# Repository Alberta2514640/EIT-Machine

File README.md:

# picoAWG
Arbitrary Waveform Generator for the Raspberry Pi Pico 16 Channels

## AWG Desktop Application
Desktop application to interface with Arbitrary Waveform Generator

TODO
- Implement Control of 16 Channels to Control Amplitude, Frequency, Offset 
- Read Back Output with Monitor to see the output
- Control LED s as needed

## PCB Design 
The board design for the waveform generator

TODO
- Update PCB design to include RP2040 directly and a cheaper OP AMP
- Update PCB design to shrink the design down to a more reasonable size and add a small status display beyond the current 5 status LEDs.

## RP2040 Code 
The code loaded onto the Pi Pico. 

TODO
- Monitor Output Needs to be fixed to setup the output
    - Write Values to the Output and Read Corresponding Voltage Changes 
- Control over channels 1-16 with Output Adjustments
    - Split the ADC control and the communication/ led control to seperate cores communicating between one another.
    - Utilize the PIO to drive the SPI peripheral and set the outputs appropriately. 
- Add functions to set the Configuration Register, Offset, Calibration, Data, Registers

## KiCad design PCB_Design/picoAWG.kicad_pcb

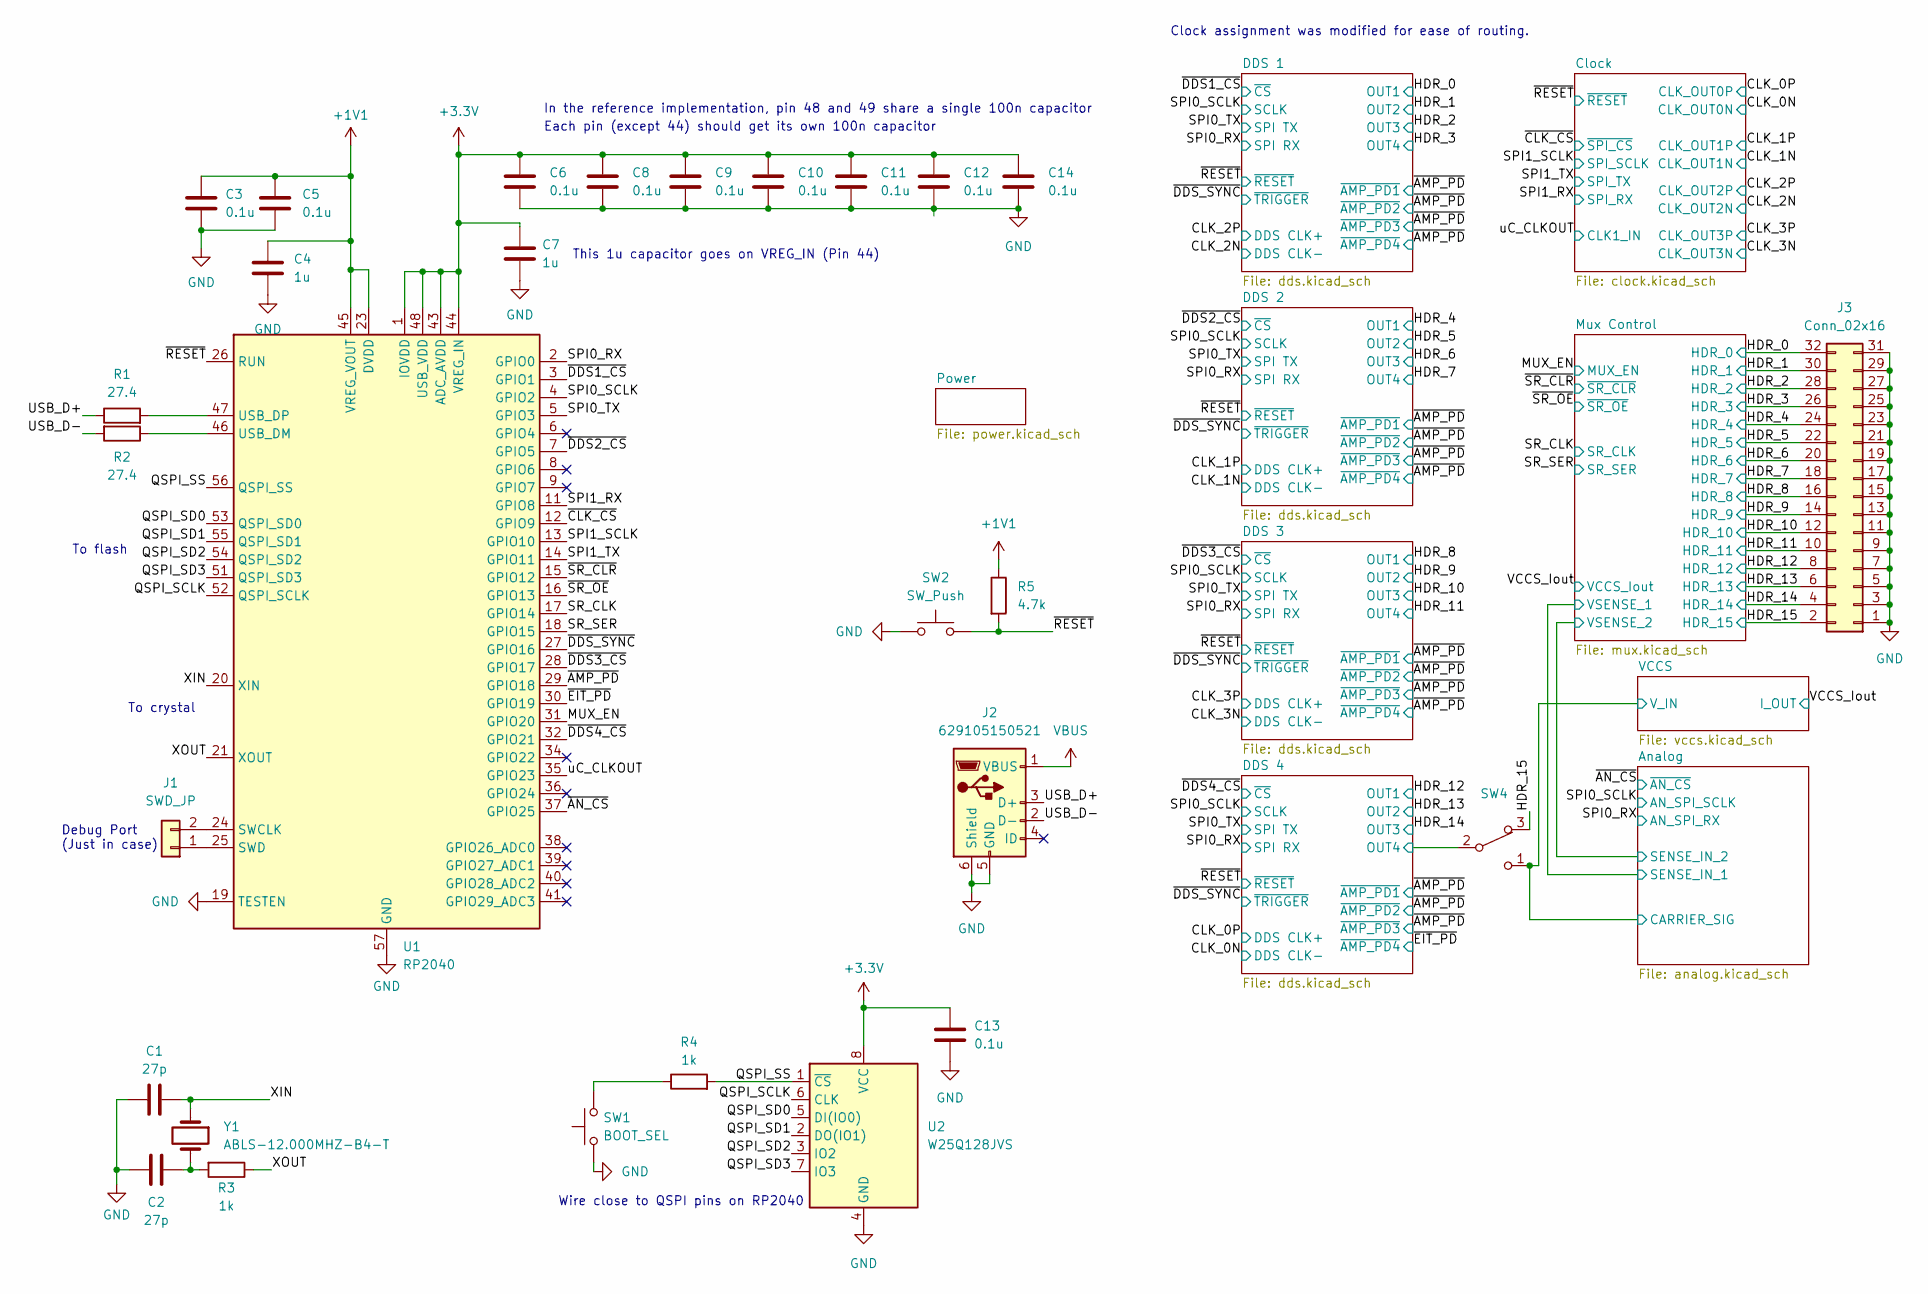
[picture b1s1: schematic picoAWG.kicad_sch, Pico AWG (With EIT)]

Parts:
C1, C2: 27p; C_0603_1608Metric
C3, C5, C6, C8, C9, C10, C11, C12, C13, C14: 0.1u; C_0603_1608Metric
C4, C7: 1u; C_0603_1608Metric
J1: SWD_JP; PinSocket_1x02_P1.00mm_Vertical
J2: 629105150521; USB_Micro-B_Amphenol_10118193-0001LF_Horizontal
J3: Conn_02x16; PinHeader_2x16_P2.54mm_Vertical
R1, R2: 27.4; R_0603_1608Metric
R3, R4: 1k; R_0603_1608Metric
R5: 4.7k; R_0603_1608Metric
SW1: BOOT_SEL; SW_Push_SPST_NO_Alps_SKRK
SW2: SW_Push; SW_Push_SPST_NO_Alps_SKRK
SW4: SW_SPDT_321; SW_E-Switch_EG1271_SPDT
U1: RP2040; QFN-56-1EP_7x7mm_P0.4mm_EP3.2x3.2mm
U2: W25Q128JVS; SOIC-8_5.23x5.23mm_P1.27mm
Y1: ABLS-12.000MHZ-B4-T; Crystal_SMD_HC49-SD

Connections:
+1V1: C3.1, C4.1, C5.1, R5.1, U1.23 (DVDD), U1.45 (VREG_VOUT), U1.50 (DVDD)
+3.3V: C6.1, C7.1, C8.1, C9.1, C10.1, C11.1, C12.1, C13.1, C14.1, U1.1 (IOVDD), U1.10 (IOVDD), U1.22 (IOVDD), U1.33 (IOVDD), U1.42 (IOVDD), U1.43 (ADC_AVDD), U1.44 (VREG_IN), U1.48 (USB_VDD), U1.49 (IOVDD), U2.8 (VCC); also elsewhere on the board
/Analog/CARRIER_SIG: SW4.1 (C); also elsewhere on the board
/DDS 4/OUT4: SW4.2 (B); also elsewhere on the board
/HDR_0: J3.32; also elsewhere on the board
/HDR_1: J3.30; also elsewhere on the board
/HDR_2: J3.28; also elsewhere on the board
/HDR_3: J3.26; also elsewhere on the board
/HDR_4: J3.24; also elsewhere on the board
/HDR_5: J3.22; also elsewhere on the board
/HDR_6: J3.20; also elsewhere on the board
/HDR_7: J3.18; also elsewhere on the board
/HDR_8: J3.16; also elsewhere on the board
/HDR_9: J3.14; also elsewhere on the board
/HDR_10: J3.12; also elsewhere on the board
/HDR_11: J3.10; also elsewhere on the board
/HDR_12: J3.8; also elsewhere on the board
/HDR_13: J3.6; also elsewhere on the board
/HDR_14: J3.4; also elsewhere on the board
/HDR_15: J3.2, SW4.3 (A); also elsewhere on the board
/MUX_EN: U1.31 (GPIO20); also elsewhere on the board
/QSPI_SCLK: U1.52 (QSPI_SCLK), U2.6 (CLK)
/QSPI_SD0: U1.53 (QSPI_SD0), U2.5 (DI(IO0))
/QSPI_SD1: U1.55 (QSPI_SD1), U2.2 (DO(IO1))
/QSPI_SD2: U1.54 (QSPI_SD2), U2.3 (IO2)
/QSPI_SD3: U1.51 (QSPI_SD3), U2.7 (IO3)
/QSPI_SS: R4.2, U1.56 (QSPI_SS), U2.1 (~CS)
/SPI0_RX: U1.2 (GPIO0); also elsewhere on the board
/SPI0_SCLK: U1.4 (GPIO2); also elsewhere on the board
/SPI0_TX: U1.5 (GPIO3); also elsewhere on the board
/SPI1_RX: U1.11 (GPIO8); also elsewhere on the board
/SPI1_SCLK: U1.13 (GPIO10); also elsewhere on the board
/SPI1_TX: U1.14 (GPIO11); also elsewhere on the board
/SR_CLK: U1.17 (GPIO14); also elsewhere on the board
/SR_SER: U1.18 (GPIO15); also elsewhere on the board
/USB_D+: J2.3 (D+), R1.1
/USB_D-: J2.2 (D-), R2.2
/XIN: C1.2, U1.20 (XIN), Y1.1
/XOUT: R3.1, U1.21 (XOUT)
/uC_CLKOUT: U1.35 (GPIO23); also elsewhere on the board
/~AMP_PD: U1.29 (GPIO18); also elsewhere on the board
/~AN_CS: U1.37 (GPIO25); also elsewhere on the board
/~CLK_CS: U1.12 (GPIO9); also elsewhere on the board
/~DDS1_CS: U1.3 (GPIO1); also elsewhere on the board
/~DDS2_CS: U1.7 (GPIO5); also elsewhere on the board
/~DDS3_CS: U1.28 (GPIO17); also elsewhere on the board
/~DDS4_CS: U1.32 (GPIO21); also elsewhere on the board
/~DDS_SYNC: U1.27 (GPIO16); also elsewhere on the board
/~EIT_PD: U1.30 (GPIO19); also elsewhere on the board
/~RESET: R5.2, SW2.2, U1.26 (RUN); also elsewhere on the board
/~SR_CLR: U1.15 (GPIO12); also elsewhere on the board
/~SR_OE: U1.16 (GPIO13); also elsewhere on the board
GND: C1.1, C2.2, C3.2, C4.2, C5.2, C6.2, C7.2, C8.2, C9.2, C10.2, C11.2, C12.2, C13.2, C14.2, J2.5 (GND), J2.6 (Shield), J3.1, J3.3, J3.5, J3.7, J3.9, J3.11, J3.13, J3.15, J3.17, J3.19, J3.21, J3.23, J3.25, J3.27, J3.29, J3.31, SW1.1, SW2.1, U1.19 (TESTEN), U1.57 (GND), U2.4 (GND); also elsewhere on the board
unnamed: C2.1, R3.2, Y1.2
unnamed: J1.1, U1.25 (SWD)
unnamed: J1.2, U1.24 (SWCLK)
unnamed: R4.1, SW1.2
unnamed: R2.1, U1.46 (USB_DM)
unnamed: R1.2, U1.47 (USB_DP)
VBUS: J2.1 (VBUS); also elsewhere on the board

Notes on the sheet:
Each pin (except 44) should get its own 100n capacitor
To crystal
Debug Port (Just in case)
This 1u capacitor goes on VREG_IN (Pin 44)
To flash
Clock assignment was modified for ease of routing.
In the reference implementation, pin 48 and 49 share a single 100n capacitor
Wire close to QSPI pins on RP2040

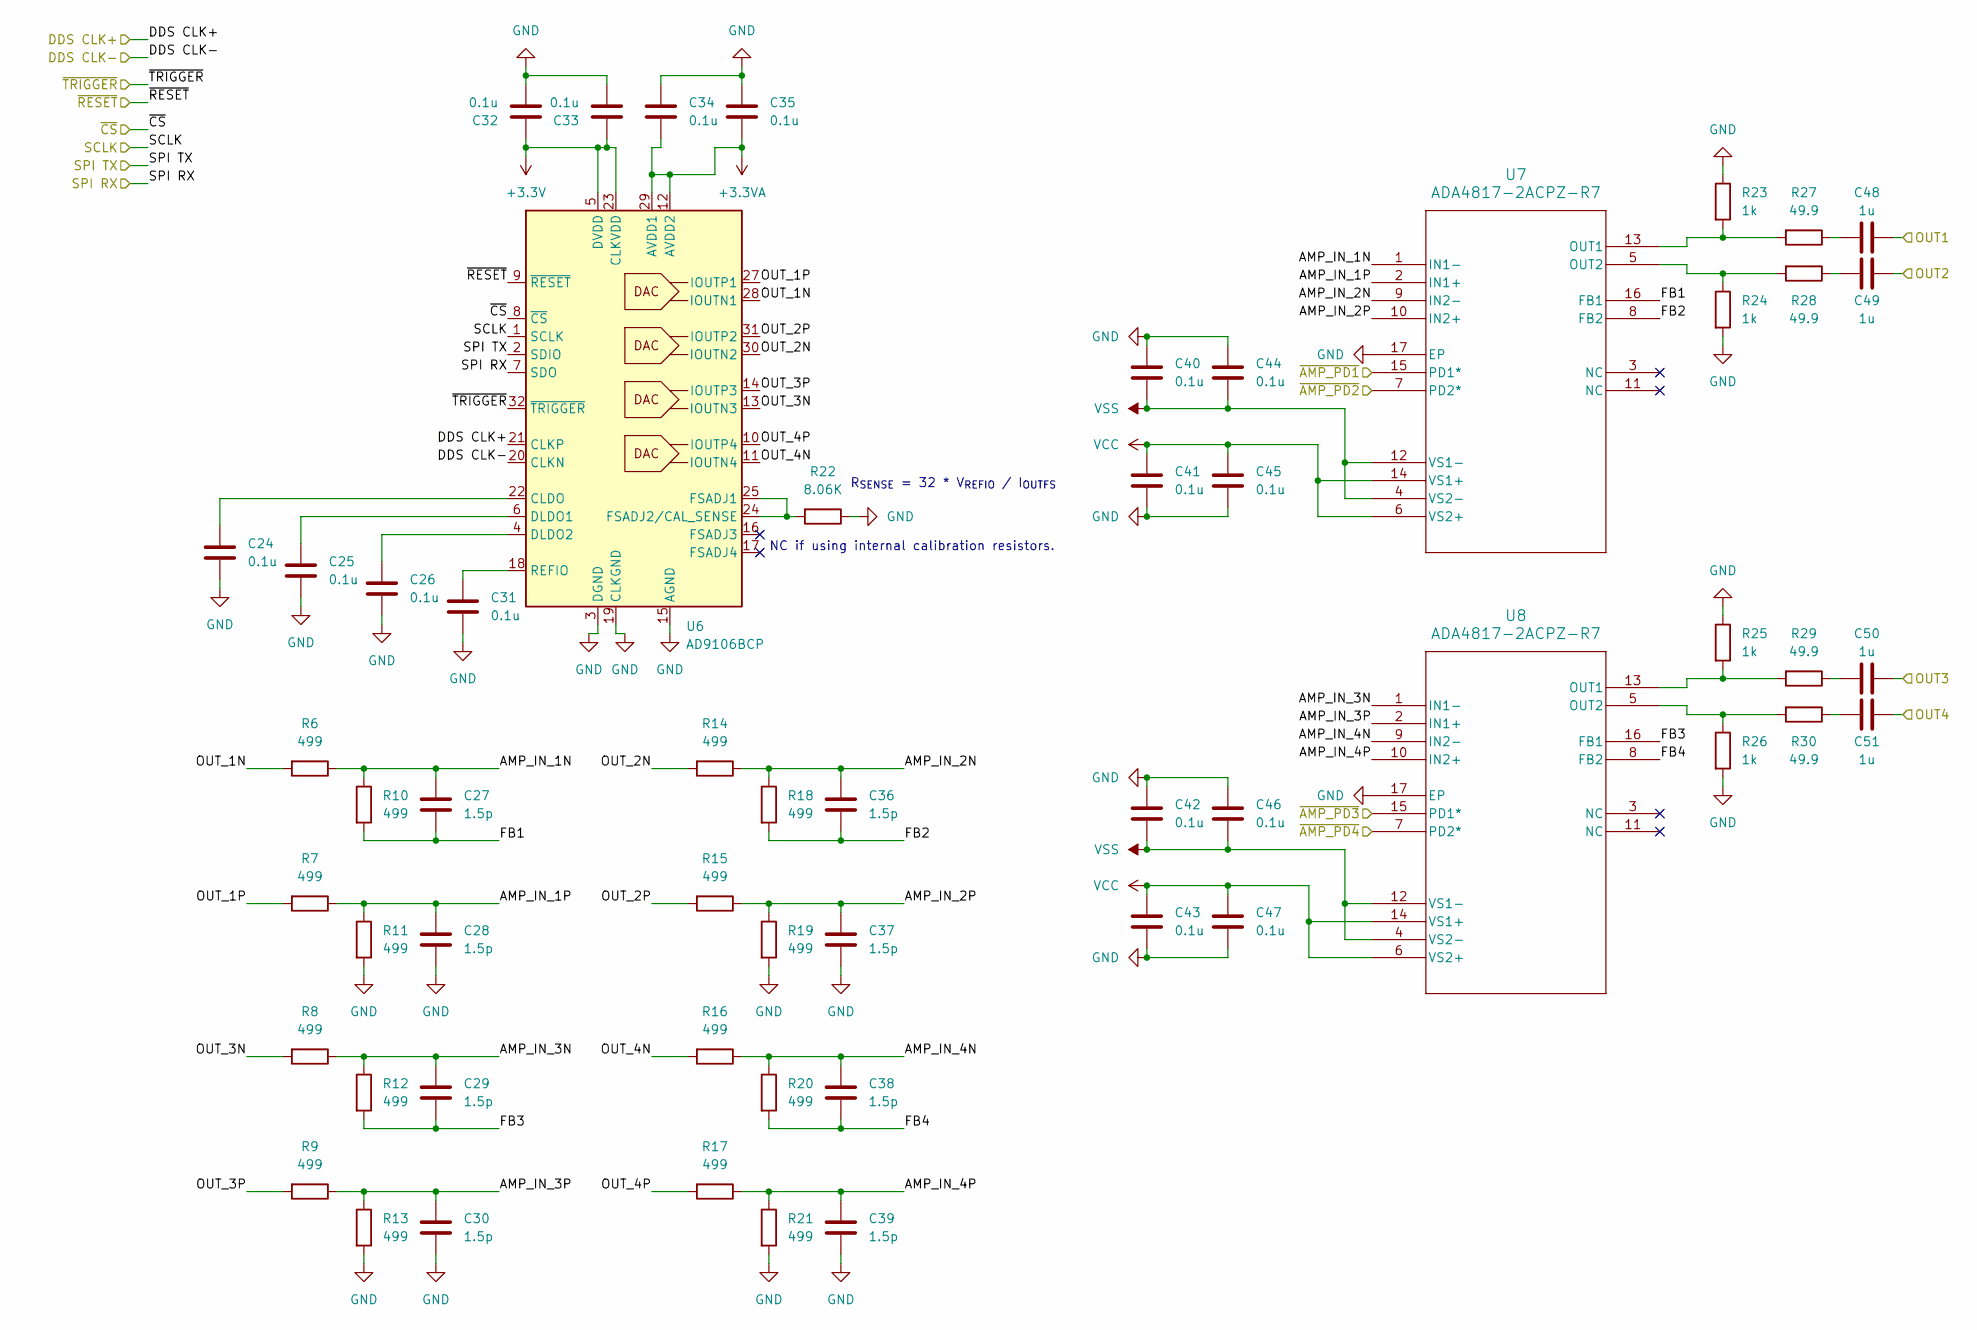
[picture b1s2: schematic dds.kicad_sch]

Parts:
C24, C25, C26, C31, C32, C33, C34, C35, C40, C41, C42, C43, C44, C45, C46, C47: 0.1u; C_0603_1608Metric
C27, C28, C29, C30, C36, C37, C38, C39: 1.5p; C_0603_1608Metric
C48, C49, C50, C51: 1u; C_0603_1608Metric
R6, R7, R8, R9, R10, R11, R12, R13, R14, R15, R16, R17, R18, R19, R20, R21: 499; R_0603_1608Metric
R22: 8.06K; R_0603_1608Metric
R23, R24, R25, R26: 1k; R_0603_1608Metric
R27, R28, R29, R30: 49.9; R_0603_1608Metric
U6: AD9106BCP; LFCSP-32-1EP_5x5mm_P0.5mm_EP3.6x3.6mm
U7, U8: ADA4817-2ACPZ-R7; CP_16_4_ADI

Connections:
+3.3V: C32.1, C33.1, U6.5 (DVDD), U6.23 (CLKVDD); also elsewhere on the board
+3.3VA: C34.2, C35.2, U6.12 (AVDD2), U6.29 (AVDD1); also elsewhere on the board
/CLK_2N: U6.20 (CLKN); also elsewhere on the board
/CLK_2P: U6.21 (CLKP); also elsewhere on the board
/DDS 1/AMP_IN_1N: C27.1, R6.1, R10.1, U7.1 (IN1-)
/DDS 1/AMP_IN_1P: C28.1, R7.1, R11.1, U7.2 (IN1+)
/DDS 1/AMP_IN_2N: C36.1, R14.1, R18.1, U7.9 (IN2-)
/DDS 1/AMP_IN_2P: C37.1, R15.1, R19.1, U7.10 (IN2+)
/DDS 1/AMP_IN_3N: C29.1, R8.1, R12.1, U8.1 (IN1-)
/DDS 1/AMP_IN_3P: C30.1, R9.1, R13.1, U8.2 (IN1+)
/DDS 1/AMP_IN_4N: C38.1, R16.1, R20.1, U8.9 (IN2-)
/DDS 1/AMP_IN_4P: C39.1, R17.1, R21.1, U8.10 (IN2+)
/DDS 1/FB1: C27.2, R10.2, U7.16 (FB1)
/DDS 1/FB2: C36.2, R18.2, U7.8 (FB2)
/DDS 1/FB3: C29.2, R12.2, U8.16 (FB1)
/DDS 1/FB4: C38.2, R20.2, U8.8 (FB2)
/DDS 1/OUT_1N: R6.2, U6.28 (IOUTN1)
/DDS 1/OUT_1P: R7.2, U6.27 (IOUTP1)
/DDS 1/OUT_2N: R14.2, U6.30 (IOUTN2)
/DDS 1/OUT_2P: R15.2, U6.31 (IOUTP2)
/DDS 1/OUT_3N: R8.2, U6.13 (IOUTN3)
/DDS 1/OUT_3P: R9.2, U6.14 (IOUTP3)
/DDS 1/OUT_4N: R16.2, U6.11 (IOUTN4)
/DDS 1/OUT_4P: R17.2, U6.10 (IOUTP4)
/HDR_0: C48.2; also elsewhere on the board
/HDR_1: C49.2; also elsewhere on the board
/HDR_2: C50.2; also elsewhere on the board
/HDR_3: C51.2; also elsewhere on the board
/SPI0_RX: U6.7 (SDO); also elsewhere on the board
/SPI0_SCLK: U6.1 (SCLK); also elsewhere on the board
/SPI0_TX: U6.2 (SDIO); also elsewhere on the board
/~AMP_PD: U7.7 (PD2*), U7.15 (PD1*), U8.7 (PD2*), U8.15 (PD1*); also elsewhere on the board
/~DDS1_CS: U6.8 (~CS); also elsewhere on the board
/~DDS_SYNC: U6.32 (~TRIGGER); also elsewhere on the board
/~RESET: U6.9 (~RESET); also elsewhere on the board
GND: C24.1, C25.1, C26.1, C28.2, C30.2, C31.1, C32.2, C33.2, C34.1, C35.1, C37.2, C39.2, C40.1, C41.2, C42.1, C43.2, C44.1, C45.2, C46.1, C47.2, R11.2, R13.2, R19.2, R21.2, R22.1, R23.1, R24.2, R25.1, R26.2, U6.3 (DGND), U6.15 (AGND), U6.19 (CLKGND), U6.26 (AGND), U6.33 (DGND), U7.17 (EP), U8.17 (EP); also elsewhere on the board
unnamed: C48.1, R27.1
unnamed: C49.1, R28.1
unnamed: C50.1, R29.1
unnamed: C51.1, R30.1
unnamed: C24.2, U6.22 (CLDO)
unnamed: C25.2, U6.6 (DLDO1)
unnamed: C26.2, U6.4 (DLDO2)
unnamed: R22.2, U6.24 (FSADJ2/CAL_SENSE), U6.25 (FSADJ1)
unnamed: C31.2, U6.18 (REFIO)
unnamed: R23.2, R27.2, U7.13 (OUT1)
unnamed: R24.1, R28.2, U7.5 (OUT2)
unnamed: R25.2, R29.2, U8.13 (OUT1)
unnamed: R26.1, R30.2, U8.5 (OUT2)
VCC: C41.1, C43.1, C45.1, C47.1, U7.6 (VS2+), U7.14 (VS1+), U8.6 (VS2+), U8.14 (VS1+); also elsewhere on the board
VSS: C40.2, C42.2, C44.2, C46.2, U7.4 (VS2-), U7.12 (VS1-), U8.4 (VS2-), U8.12 (VS1-); also elsewhere on the board

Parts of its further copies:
C52, C53, C54, C59, C60, C61, C62, C63, C68, C69, C70, C71, C72, C73, C74, C75, C80, C81, C82, C87, C88, C89, C90, C91, C96, C97, C98, C99, C100, C101, C102, C103, C108, C109, C110, C115, C116, C117, C118, C119, C124, C125, C126, C127, C128, C129, C130, C131: 0.1u; C_0603_1608Metric
C55, C56, C57, C58, C64, C65, C66, C67, C83, C84, C85, C86, C92, C93, C94, C95, C111, C112, C113, C114, C120, C121, C122, C123: 1.5p; C_0603_1608Metric
C76, C77, C78, C79, C104, C105, C106, C107, C132, C133, C134, C135: 1u; C_0603_1608Metric
R31, R32, R33, R34, R35, R36, R37, R38, R39, R40, R41, R42, R43, R44, R45, R46, R56, R57, R58, R59, R60, R61, R62, R63, R64, R65, R66, R67, R68, R69, R70, R71, R81, R82, R83, R84, R85, R86, R87, R88, R89, R90, R91, R92, R93, R94, R95, R96: 499; R_0603_1608Metric
R47, R72, R97: 8.06K; R_0603_1608Metric
R48, R49, R50, R51, R73, R74, R75, R76, R98, R99, R100, R101: 1k; R_0603_1608Metric
R52, R53, R54, R55, R77, R78, R79, R80, R102, R103, R104, R105: 49.9; R_0603_1608Metric
U9, U12, U15: AD9106BCP; LFCSP-32-1EP_5x5mm_P0.5mm_EP3.6x3.6mm
U10, U11, U13, U14, U16, U17: ADA4817-2ACPZ-R7; CP_16_4_ADI

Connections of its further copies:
+3.3V: C60.1, C61.1, C88.1, C89.1, C116.1, C117.1, U9.5 (DVDD), U9.23 (CLKVDD), U12.5 (DVDD), U12.23 (CLKVDD), U15.5 (DVDD), U15.23 (CLKVDD); also elsewhere on the board
+3.3VA: C62.2, C63.2, C90.2, C91.2, C118.2, C119.2, U9.12 (AVDD2), U9.29 (AVDD1), U12.12 (AVDD2), U12.29 (AVDD1), U15.12 (AVDD2), U15.29 (AVDD1); also elsewhere on the board
/CLK_0N: U15.20 (CLKN); also elsewhere on the board
/CLK_0P: U15.21 (CLKP); also elsewhere on the board
/CLK_1N: U9.20 (CLKN); also elsewhere on the board
/CLK_1P: U9.21 (CLKP); also elsewhere on the board
/CLK_3N: U12.20 (CLKN); also elsewhere on the board
/CLK_3P: U12.21 (CLKP); also elsewhere on the board
/DDS 2/AMP_IN_1N: C55.1, R31.1, R35.1, U10.1 (IN1-)
/DDS 2/AMP_IN_1P: C56.1, R32.1, R36.1, U10.2 (IN1+)
/DDS 2/AMP_IN_2N: C64.1, R39.1, R43.1, U10.9 (IN2-)
/DDS 2/AMP_IN_2P: C65.1, R40.1, R44.1, U10.10 (IN2+)
/DDS 2/AMP_IN_3N: C57.1, R33.1, R37.1, U11.1 (IN1-)
/DDS 2/AMP_IN_3P: C58.1, R34.1, R38.1, U11.2 (IN1+)
/DDS 2/AMP_IN_4N: C66.1, R41.1, R45.1, U11.9 (IN2-)
/DDS 2/AMP_IN_4P: C67.1, R42.1, R46.1, U11.10 (IN2+)
/DDS 2/FB1: C55.2, R35.2, U10.16 (FB1)
/DDS 2/FB2: C64.2, R43.2, U10.8 (FB2)
/DDS 2/FB3: C57.2, R37.2, U11.16 (FB1)
/DDS 2/FB4: C66.2, R45.2, U11.8 (FB2)
/DDS 2/OUT_1N: R31.2, U9.28 (IOUTN1)
/DDS 2/OUT_1P: R32.2, U9.27 (IOUTP1)
/DDS 2/OUT_2N: R39.2, U9.30 (IOUTN2)
/DDS 2/OUT_2P: R40.2, U9.31 (IOUTP2)
/DDS 2/OUT_3N: R33.2, U9.13 (IOUTN3)
/DDS 2/OUT_3P: R34.2, U9.14 (IOUTP3)
/DDS 2/OUT_4N: R41.2, U9.11 (IOUTN4)
/DDS 2/OUT_4P: R42.2, U9.10 (IOUTP4)
/DDS 3/AMP_IN_1N: C83.1, R56.1, R60.1, U13.1 (IN1-)
/DDS 3/AMP_IN_1P: C84.1, R57.1, R61.1, U13.2 (IN1+)
/DDS 3/AMP_IN_2N: C92.1, R64.1, R68.1, U13.9 (IN2-)
/DDS 3/AMP_IN_2P: C93.1, R65.1, R69.1, U13.10 (IN2+)
/DDS 3/AMP_IN_3N: C85.1, R58.1, R62.1, U14.1 (IN1-)
/DDS 3/AMP_IN_3P: C86.1, R59.1, R63.1, U14.2 (IN1+)
/DDS 3/AMP_IN_4N: C94.1, R66.1, R70.1, U14.9 (IN2-)
/DDS 3/AMP_IN_4P: C95.1, R67.1, R71.1, U14.10 (IN2+)
/DDS 3/FB1: C83.2, R60.2, U13.16 (FB1)
/DDS 3/FB2: C92.2, R68.2, U13.8 (FB2)
/DDS 3/FB3: C85.2, R62.2, U14.16 (FB1)
/DDS 3/FB4: C94.2, R70.2, U14.8 (FB2)
/DDS 3/OUT_1N: R56.2, U12.28 (IOUTN1)
/DDS 3/OUT_1P: R57.2, U12.27 (IOUTP1)
/DDS 3/OUT_2N: R64.2, U12.30 (IOUTN2)
/DDS 3/OUT_2P: R65.2, U12.31 (IOUTP2)
/DDS 3/OUT_3N: R58.2, U12.13 (IOUTN3)
/DDS 3/OUT_3P: R59.2, U12.14 (IOUTP3)
/DDS 3/OUT_4N: R66.2, U12.11 (IOUTN4)
/DDS 3/OUT_4P: R67.2, U12.10 (IOUTP4)
/DDS 4/AMP_IN_1N: C111.1, R81.1, R85.1, U16.1 (IN1-)
/DDS 4/AMP_IN_1P: C112.1, R82.1, R86.1, U16.2 (IN1+)
/DDS 4/AMP_IN_2N: C120.1, R89.1, R93.1, U16.9 (IN2-)
/DDS 4/AMP_IN_2P: C121.1, R90.1, R94.1, U16.10 (IN2+)
/DDS 4/AMP_IN_3N: C113.1, R83.1, R87.1, U17.1 (IN1-)
/DDS 4/AMP_IN_3P: C114.1, R84.1, R88.1, U17.2 (IN1+)
/DDS 4/AMP_IN_4N: C122.1, R91.1, R95.1, U17.9 (IN2-)
/DDS 4/AMP_IN_4P: C123.1, R92.1, R96.1, U17.10 (IN2+)
/DDS 4/FB1: C111.2, R85.2, U16.16 (FB1)
/DDS 4/FB2: C120.2, R93.2, U16.8 (FB2)
/DDS 4/FB3: C113.2, R87.2, U17.16 (FB1)
/DDS 4/FB4: C122.2, R95.2, U17.8 (FB2)
/DDS 4/OUT4: C135.2; also elsewhere on the board
/DDS 4/OUT_1N: R81.2, U15.28 (IOUTN1)
/DDS 4/OUT_1P: R82.2, U15.27 (IOUTP1)
/DDS 4/OUT_2N: R89.2, U15.30 (IOUTN2)
/DDS 4/OUT_2P: R90.2, U15.31 (IOUTP2)
/DDS 4/OUT_3N: R83.2, U15.13 (IOUTN3)
/DDS 4/OUT_3P: R84.2, U15.14 (IOUTP3)
/DDS 4/OUT_4N: R91.2, U15.11 (IOUTN4)
/DDS 4/OUT_4P: R92.2, U15.10 (IOUTP4)
/HDR_4: C76.2; also elsewhere on the board
/HDR_5: C77.2; also elsewhere on the board
/HDR_6: C78.2; also elsewhere on the board
/HDR_7: C79.2; also elsewhere on the board
/HDR_8: C104.2; also elsewhere on the board
/HDR_9: C105.2; also elsewhere on the board
/HDR_10: C106.2; also elsewhere on the board
/HDR_11: C107.2; also elsewhere on the board
/HDR_12: C132.2; also elsewhere on the board
/HDR_13: C133.2; also elsewhere on the board
/HDR_14: C134.2; also elsewhere on the board
/SPI0_RX: U9.7 (SDO), U12.7 (SDO), U15.7 (SDO); also elsewhere on the board
/SPI0_SCLK: U9.1 (SCLK), U12.1 (SCLK), U15.1 (SCLK); also elsewhere on the board
/SPI0_TX: U9.2 (SDIO), U12.2 (SDIO), U15.2 (SDIO); also elsewhere on the board
/~AMP_PD: U10.7 (PD2*), U10.15 (PD1*), U11.7 (PD2*), U11.15 (PD1*), U13.7 (PD2*), U13.15 (PD1*), U14.7 (PD2*), U14.15 (PD1*), U16.7 (PD2*), U16.15 (PD1*), U17.15 (PD1*); also elsewhere on the board
/~DDS2_CS: U9.8 (~CS); also elsewhere on the board
/~DDS3_CS: U12.8 (~CS); also elsewhere on the board
/~DDS4_CS: U15.8 (~CS); also elsewhere on the board
/~DDS_SYNC: U9.32 (~TRIGGER), U12.32 (~TRIGGER), U15.32 (~TRIGGER); also elsewhere on the board
/~EIT_PD: U17.7 (PD2*); also elsewhere on the board
/~RESET: U9.9 (~RESET), U12.9 (~RESET), U15.9 (~RESET); also elsewhere on the board
GND: C52.1, C53.1, C54.1, C56.2, C58.2, C59.1, C60.2, C61.2, C62.1, C63.1, C65.2, C67.2, C68.1, C69.2, C70.1, C71.2, C72.1, C73.2, C74.1, C75.2, C80.1, C81.1, C82.1, C84.2, C86.2, C87.1, C88.2, C89.2, C90.1, C91.1, C93.2, C95.2, C96.1, C97.2, C98.1, C99.2, C100.1, C101.2, C102.1, C103.2, C108.1, C109.1, C110.1, C112.2, C114.2, C115.1, C116.2, C117.2, C118.1, C119.1, C121.2, C123.2, C124.1, C125.2, C126.1, C127.2, C128.1, C129.2, C130.1, C131.2, R36.2, R38.2, R44.2, R46.2, R47.1, R48.1, R49.2, R50.1, R51.2, R61.2, R63.2, R69.2, R71.2, R72.1, R73.1, R74.2, R75.1, R76.2, R86.2, R88.2, R94.2, R96.2, R97.1, R98.1, R99.2, R100.1, R101.2, U9.3 (DGND), U9.15 (AGND), U9.19 (CLKGND), U9.26 (AGND), U9.33 (DGND), U10.17 (EP), U11.17 (EP), U12.3 (DGND), U12.15 (AGND), U12.19 (CLKGND), U12.26 (AGND), U12.33 (DGND), U13.17 (EP), U14.17 (EP), U15.3 (DGND), U15.15 (AGND), U15.19 (CLKGND), U15.26 (AGND), U15.33 (DGND), U16.17 (EP), U17.17 (EP); also elsewhere on the board
unnamed: C76.1, R52.1
unnamed: C77.1, R53.1
unnamed: C78.1, R54.1
unnamed: C79.1, R55.1
unnamed: C104.1, R77.1
unnamed: C105.1, R78.1
unnamed: C106.1, R79.1
unnamed: C107.1, R80.1
unnamed: C132.1, R102.1
unnamed: C133.1, R103.1
unnamed: C134.1, R104.1
unnamed: C135.1, R105.1
unnamed: C52.2, U9.22 (CLDO)
unnamed: C53.2, U9.6 (DLDO1)
unnamed: C54.2, U9.4 (DLDO2)
unnamed: R47.2, U9.24 (FSADJ2/CAL_SENSE), U9.25 (FSADJ1)
unnamed: C59.2, U9.18 (REFIO)
unnamed: R48.2, R52.2, U10.13 (OUT1)
unnamed: R49.1, R53.2, U10.5 (OUT2)
unnamed: R50.2, R54.2, U11.13 (OUT1)
unnamed: R51.1, R55.2, U11.5 (OUT2)
unnamed: C80.2, U12.22 (CLDO)
unnamed: C81.2, U12.6 (DLDO1)
unnamed: C82.2, U12.4 (DLDO2)
unnamed: R72.2, U12.24 (FSADJ2/CAL_SENSE), U12.25 (FSADJ1)
unnamed: C87.2, U12.18 (REFIO)
unnamed: R73.2, R77.2, U13.13 (OUT1)
unnamed: R74.1, R78.2, U13.5 (OUT2)
unnamed: R75.2, R79.2, U14.13 (OUT1)
unnamed: R76.1, R80.2, U14.5 (OUT2)
unnamed: C108.2, U15.22 (CLDO)
unnamed: C109.2, U15.6 (DLDO1)
unnamed: C110.2, U15.4 (DLDO2)
unnamed: R97.2, U15.24 (FSADJ2/CAL_SENSE), U15.25 (FSADJ1)
unnamed: C115.2, U15.18 (REFIO)
unnamed: R98.2, R102.2, U16.13 (OUT1)
unnamed: R99.1, R103.2, U16.5 (OUT2)
unnamed: R100.2, R104.2, U17.13 (OUT1)
unnamed: R101.1, R105.2, U17.5 (OUT2)
VCC: C69.1, C71.1, C73.1, C75.1, C97.1, C99.1, C101.1, C103.1, C125.1, C127.1, C129.1, C131.1, U10.6 (VS2+), U10.14 (VS1+), U11.6 (VS2+), U11.14 (VS1+), U13.6 (VS2+), U13.14 (VS1+), U14.6 (VS2+), U14.14 (VS1+), U16.6 (VS2+), U16.14 (VS1+), U17.6 (VS2+), U17.14 (VS1+); also elsewhere on the board
VSS: C68.2, C70.2, C72.2, C74.2, C96.2, C98.2, C100.2, C102.2, C124.2, C126.2, C128.2, C130.2, U10.4 (VS2-), U10.12 (VS1-), U11.4 (VS2-), U11.12 (VS1-), U13.4 (VS2-), U13.12 (VS1-), U14.4 (VS2-), U14.12 (VS1-), U16.4 (VS2-), U16.12 (VS1-), U17.4 (VS2-), U17.12 (VS1-); also elsewhere on the board

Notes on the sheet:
R_{SENSE} = 32 * V_{REFIO} / I_{OUTFS}
NC if using internal calibration resistors.

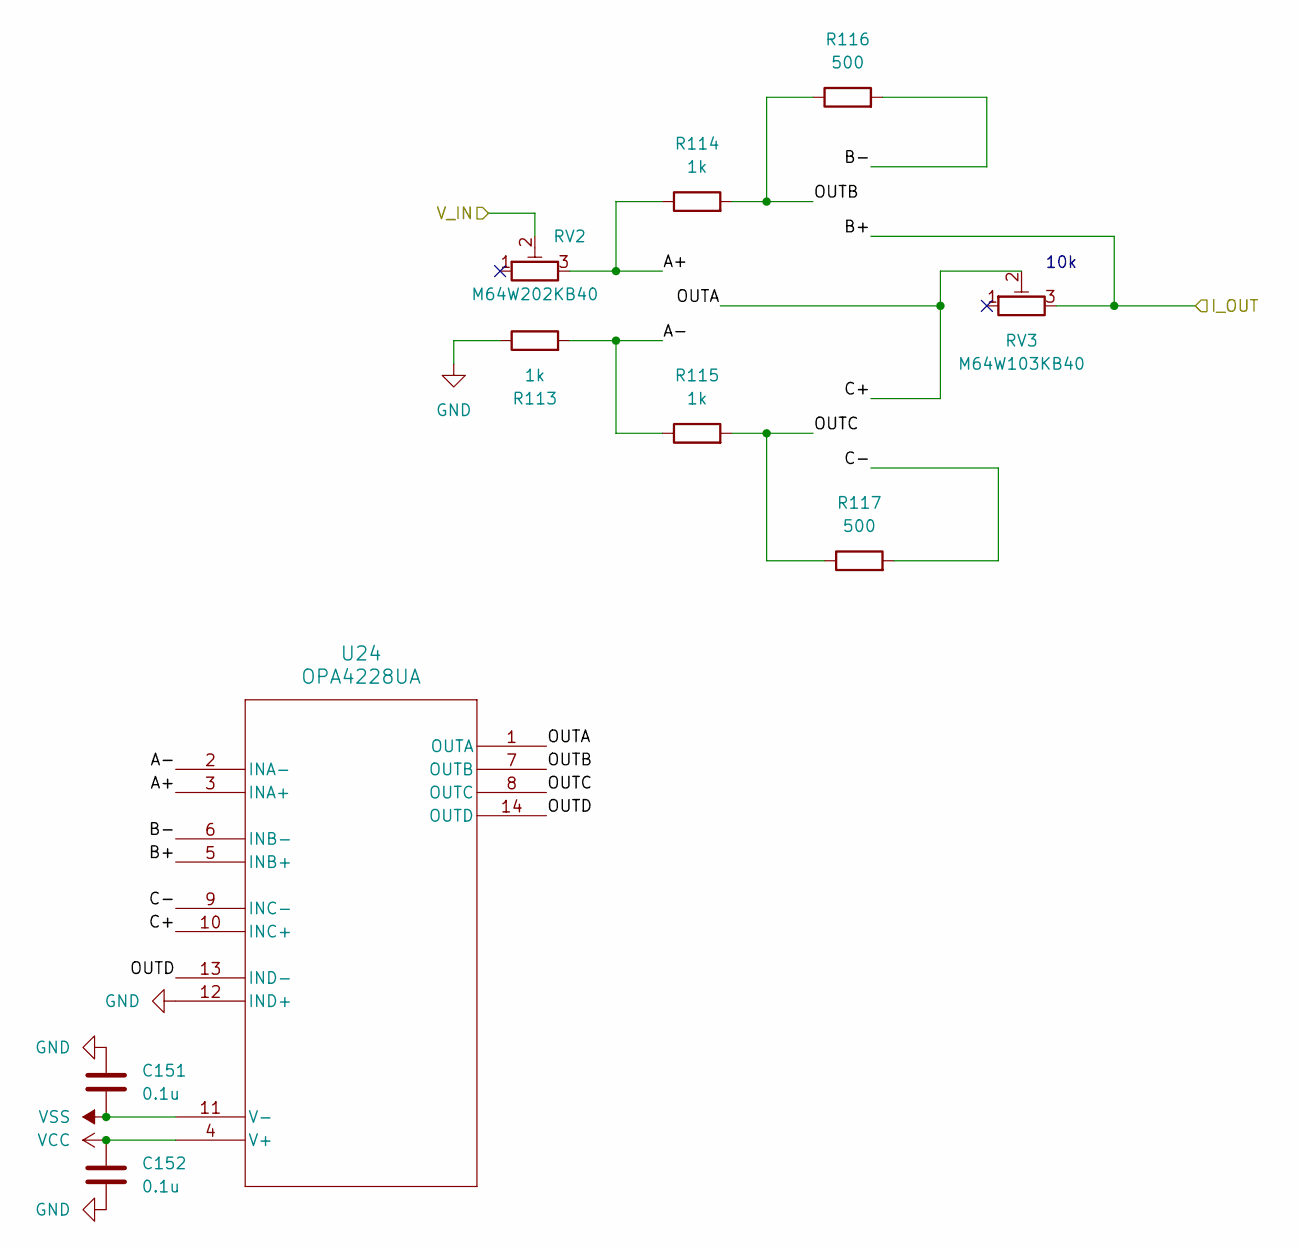
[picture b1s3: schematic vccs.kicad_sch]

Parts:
C151, C152: 0.1u; C_0603_1608Metric
R113, R114, R115: 1k; R_0603_1608Metric
R116, R117: 500; R_0603_1608Metric
RV2: M64W202KB40; POT_2023-08-01_VIS
RV3: M64W103KB40; POT_2023-08-01_VIS
U24: OPA4228UA; D14

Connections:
/Analog/CARRIER_SIG: RV2.2; also elsewhere on the board
/VCCS/A+: R114.1, RV2.3, U24.3 (INA+)
/VCCS/A-: R113.2, R115.1, U24.2 (INA-)
/VCCS/B-: R116.2, U24.6 (INB-)
/VCCS/C+: RV3.2, U24.1 (OUTA), U24.10 (INC+)
/VCCS/C-: R117.2, U24.9 (INC-)
/VCCS/OUTB: R114.2, R116.1, U24.7 (OUTB)
/VCCS/OUTC: R115.2, R117.1, U24.8 (OUTC)
/VCCS/OUTD: U24.13 (IND-), U24.14 (OUTD)
/VCCS_Iout: RV3.3, U24.5 (INB+); also elsewhere on the board
GND: C151.1, C152.2, R113.1, U24.12 (IND+); also elsewhere on the board
VCC: C152.1, U24.4 (V+); also elsewhere on the board
VSS: C151.2, U24.11 (V-); also elsewhere on the board

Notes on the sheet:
10k

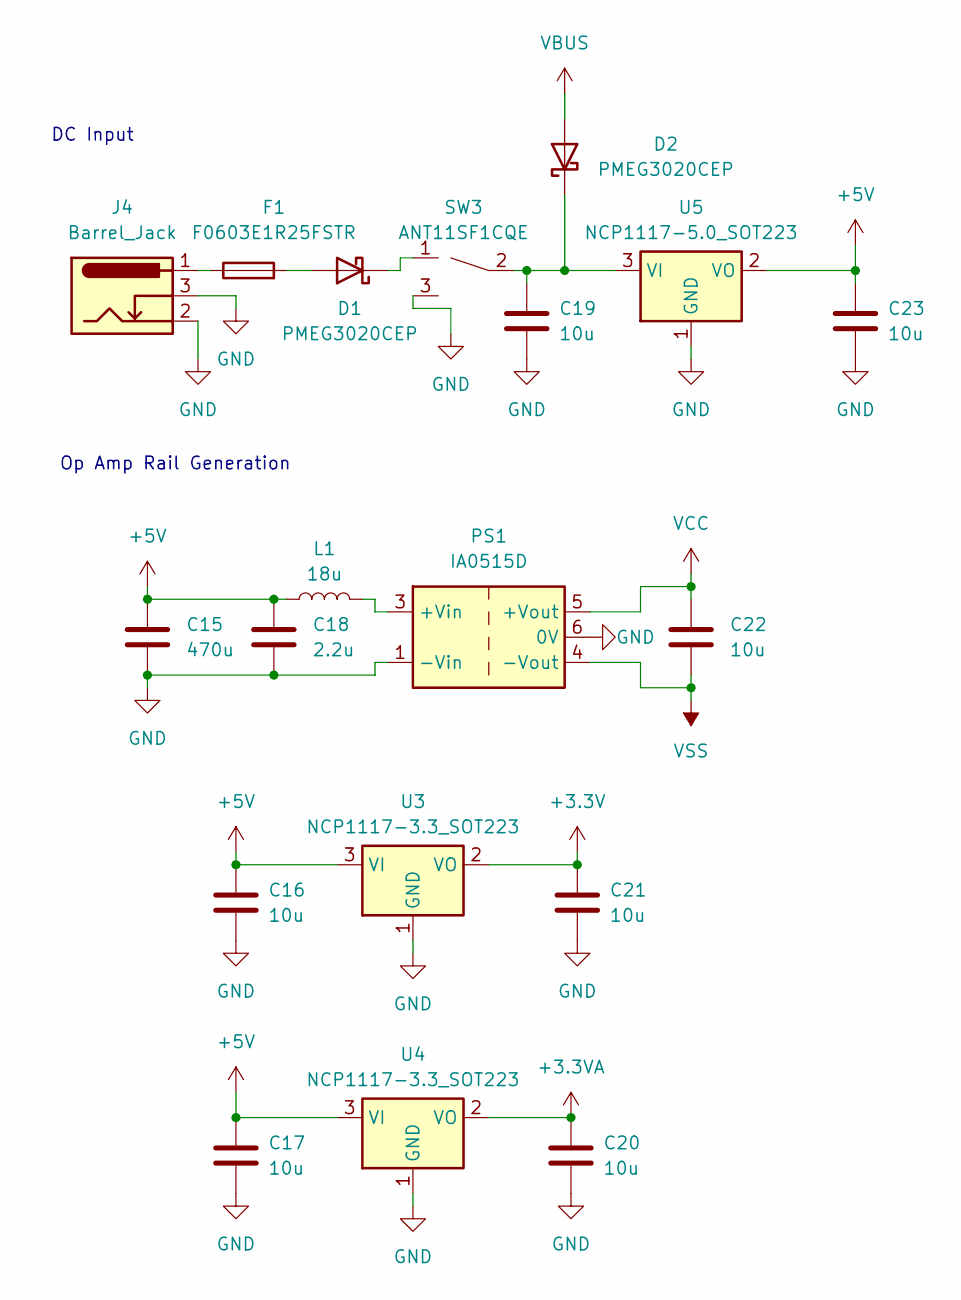
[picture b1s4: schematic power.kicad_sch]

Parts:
C15: 470u; CP_Radial_D6.3mm_P2.50mm
C16, C17, C19, C20, C21, C22, C23: 10u; C_0603_1608Metric
C18: 2.2u; C_0603_1608Metric
D1, D2: PMEG3020CEP; D_0603_1608Metric
F1: F0603E1R25FSTR; Fuse_0603_1608Metric
J4: Barrel_Jack; BarrelJack_GCT_DCJ200-10-A_Horizontal
L1: 18u; L_0603_1608Metric
PS1: IA0515D; Converter_DCDC_XP_POWER-IAxxxxD_THT
SW3: ANT11SF1CQE
U3, U4: NCP1117-3.3_SOT223; SOT-223-3_TabPin2
U5: NCP1117-5.0_SOT223; SOT-223-3_TabPin2

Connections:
+3.3V: C21.1, U3.2 (VO); also elsewhere on the board
+3.3VA: C20.1, U4.2 (VO); also elsewhere on the board
+5V: C15.1, C16.1, C17.1, C18.1, C23.1, L1.1, U3.3 (VI), U4.3 (VI), U5.2 (VO)
GND: C15.2, C16.2, C17.2, C18.2, C19.2, C20.2, C21.2, C23.2, J4.2, J4.3, PS1.1 (-Vin), PS1.6 (0V), SW3.3, U3.1 (GND), U4.1 (GND), U5.1 (GND); also elsewhere on the board
unnamed: D1.2 (A), F1.2
unnamed: D1.1 (K), SW3.1
unnamed: C19.1, D2.1 (K), SW3.2, U5.3 (VI)
unnamed: F1.1, J4.1
unnamed: L1.2, PS1.3 (+Vin)
VBUS: D2.2 (A); also elsewhere on the board
VCC: C22.1, PS1.5 (+Vout); also elsewhere on the board
VSS: C22.2, PS1.4 (-Vout); also elsewhere on the board

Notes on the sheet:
DC Input
Op Amp Rail Generation
